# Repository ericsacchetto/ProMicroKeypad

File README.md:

# ProMicroKeypad

The Pro Micro Keypad uses 9 switches to drive Windows shortcuts.
It is based on the Arduino Pro Micro (ATMega 32u4).

Nine Cherry MX Keys were used, turning on the corresponding LED for brief period of time once the ky is pressed.

A rotary encoder was included in order to easily control the volume.

The HID library https://github.com/NicoHood/HID was used, which provided an easy implementation of the shortcut key code.

All the schematic and PCB design were done using KiCad.

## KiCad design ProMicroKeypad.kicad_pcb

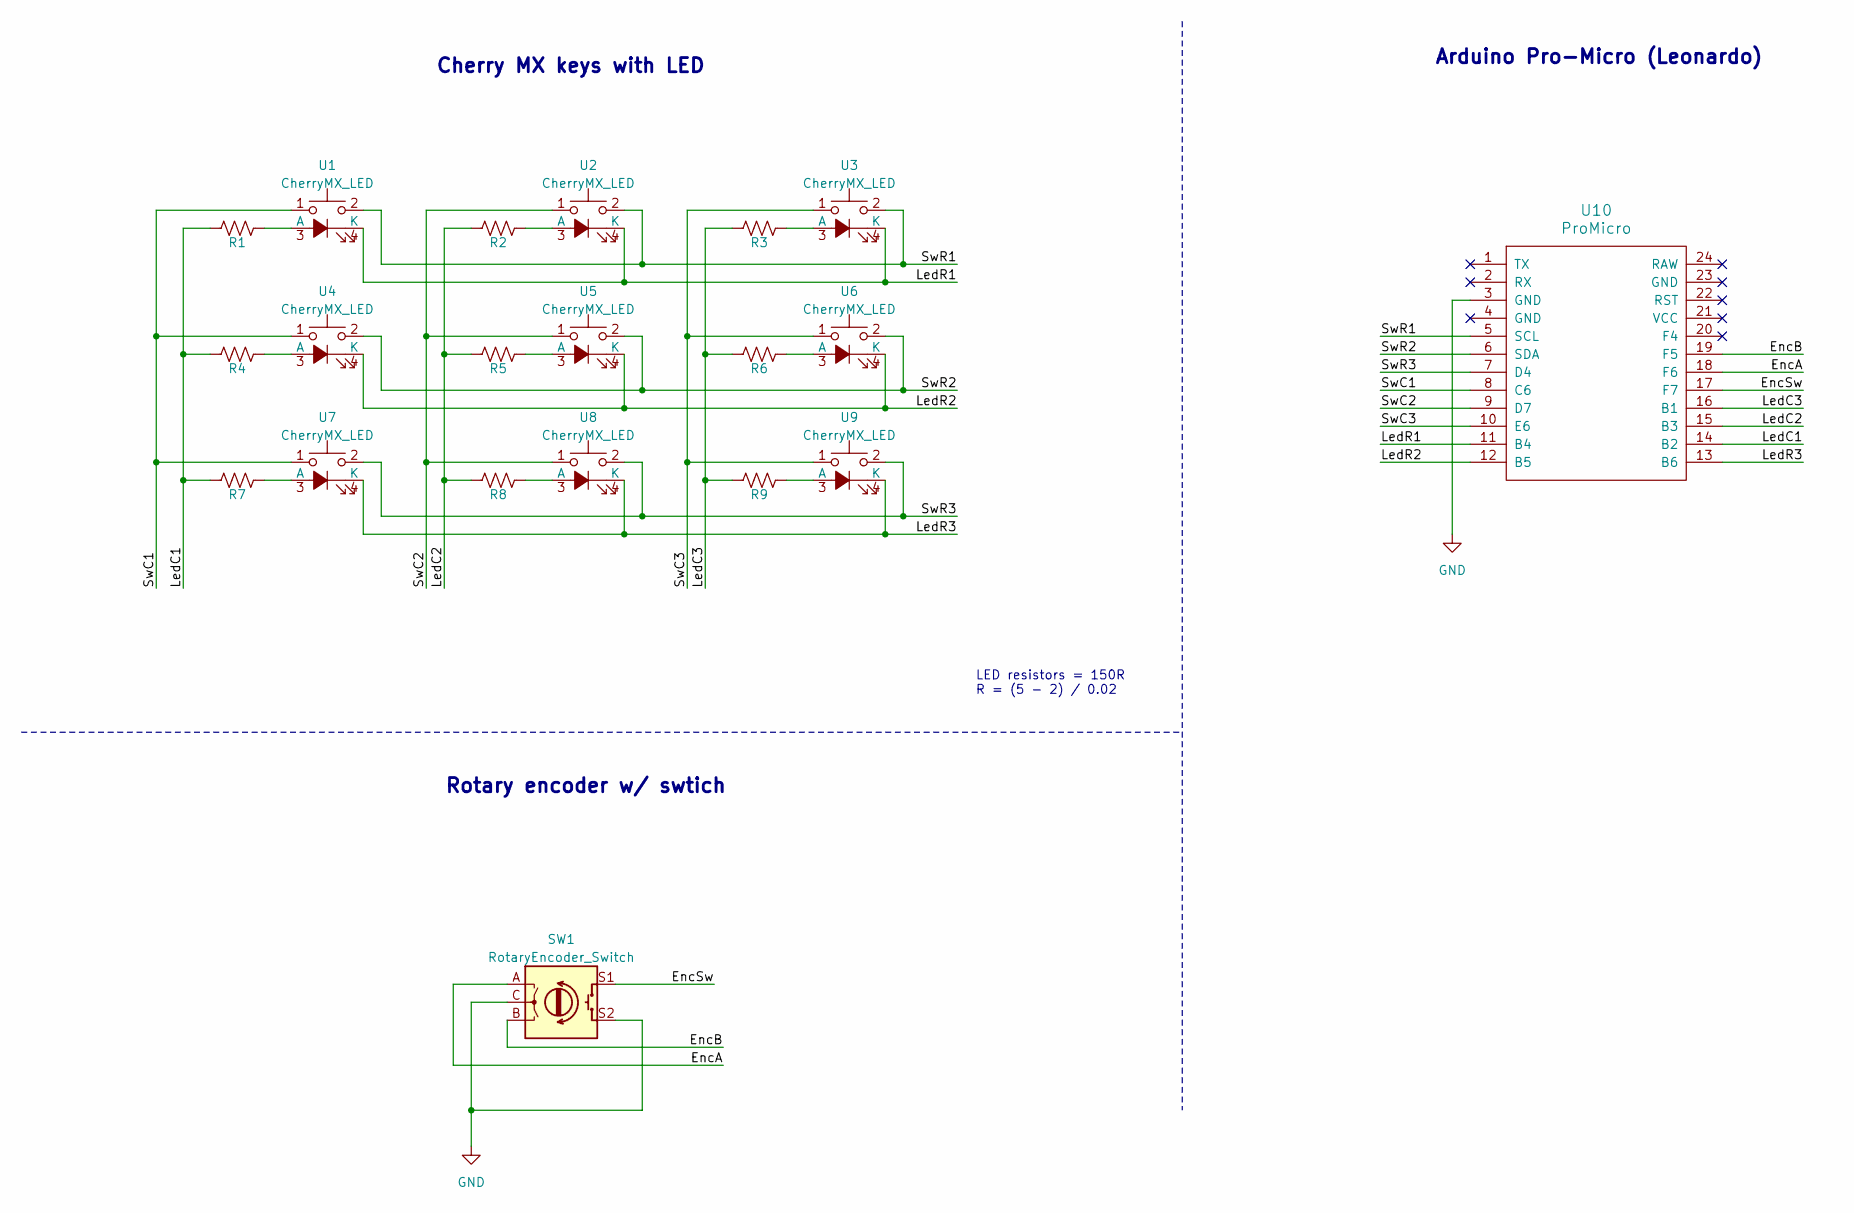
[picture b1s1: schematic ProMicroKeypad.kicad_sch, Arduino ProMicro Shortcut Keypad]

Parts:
R1, R2, R3, R4, R5, R6, R7, R8, R9: 150R; R_1206_3216Metric_Pad1.30x1.75mm_HandSolder
SW1: RotaryEncoder_Switch; RotaryEncoder_Alps_EC11E-Switch_Vertical_H20mm
U1, U2, U3, U4, U5, U6, U7, U8, U9: CherryMX_LED; CherryMX_1.00u_PCB_LED
U10: ProMicro

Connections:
/EncA: SW1.A, U10.18 (F6)
/EncB: SW1.B, U10.19 (F5)
/EncSw: SW1.S1, U10.17 (F7)
/LedC1: R1.1, R4.1, R7.1, U10.14 (B2)
/LedC2: R2.1, R5.1, R8.1, U10.15 (B3)
/LedC3: R3.1, R6.1, R9.1, U10.16 (B1)
/LedR1: U1.4 (A), U2.4 (A), U3.4 (A), U10.11 (B4)
/LedR2: U4.4 (A), U5.4 (A), U6.4 (A), U10.12 (B5)
/LedR3: U7.4 (A), U8.4 (A), U9.4 (A), U10.13 (B6)
/SwC1: U1.1, U4.1, U7.1, U10.8 (C6)
/SwC2: U2.1, U5.1, U8.1, U10.9 (D7)
/SwC3: U3.1, U6.1, U9.1, U10.10 (E6)
/SwR1: U1.2, U2.2, U3.2, U10.5 (SCL)
/SwR2: U4.2, U5.2, U6.2, U10.6 (SDA)
/SwR3: U7.2, U8.2, U9.2, U10.7 (D4)
GND: SW1.C, SW1.S2, U10.3 (GND)
unnamed: R1.2, U1.3 (K)
unnamed: R2.2, U2.3 (K)
unnamed: R3.2, U3.3 (K)
unnamed: R4.2, U4.3 (K)
unnamed: R5.2, U5.3 (K)
unnamed: R6.2, U6.3 (K)
unnamed: R7.2, U7.3 (K)
unnamed: R8.2, U8.3 (K)
unnamed: R9.2, U9.3 (K)

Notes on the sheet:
Cherry MX keys with LED
Rotary encoder w/ swtich
LED resistors = 150R R = (5 - 2) / 0.02
Arduino Pro-Micro (Leonardo)

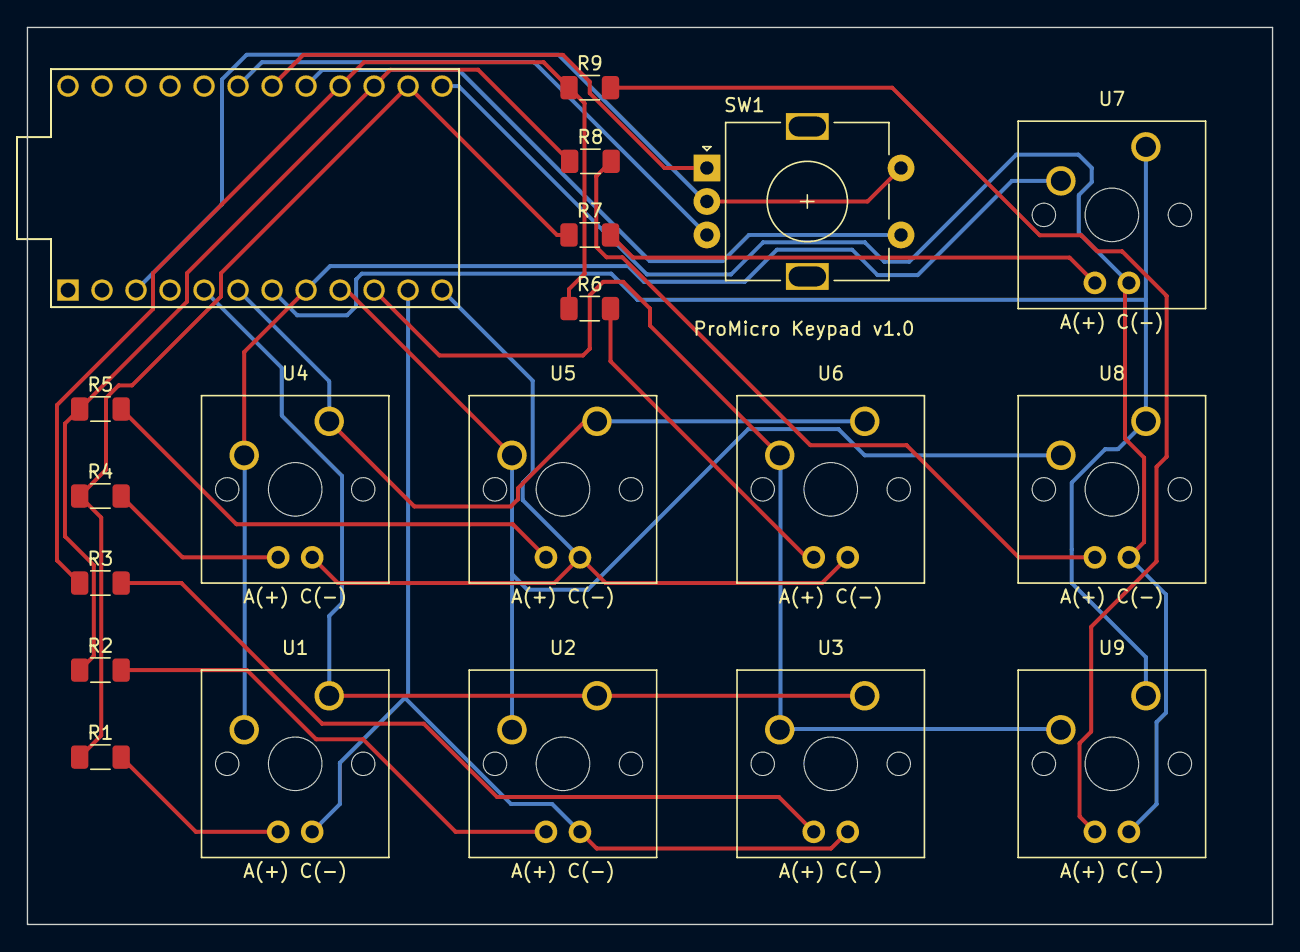
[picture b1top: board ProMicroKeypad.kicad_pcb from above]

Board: 2 copper layers, 93.0 x 67.0 mm, 20 parts (0 on the bottom side), 25 nets.

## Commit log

2021-08-11 Board completed
2021-08-11 Footprints assigned
2021-08-11 Finished component placement and annotation
2021-08-11 Components added
2021-08-11 PCB design done
2021-08-13 Uploaded the PCB PDF
2021-08-21 Fixing schematic and PCB
2021-08-22 Adding Arduino Pro code
2021-09-11 Update app name and comments
2021-11-12 Update README.md
    Updating README
2021-12-14 Removed some comments
